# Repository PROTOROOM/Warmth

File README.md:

# Warmth
The lighting place card for YoungJi & Derrick's wedding
  - PROTOROOM 
  - by SeungBum Kim & Hoonida Kim
  - 2017.04.01

이 프로젝트의 이야기는 다음 웹페이지에서 읽어볼 수 있습니다.
Please read the whole story of Warmth on the link below. (sorry for Korean only now)

https://protoroom.github.io/Warmth/memo/story_of_warmth.html

# License
 - firmware : Artistic License 2.0
 - hardware : Creative Commons Attribution ShareAlike 3.0

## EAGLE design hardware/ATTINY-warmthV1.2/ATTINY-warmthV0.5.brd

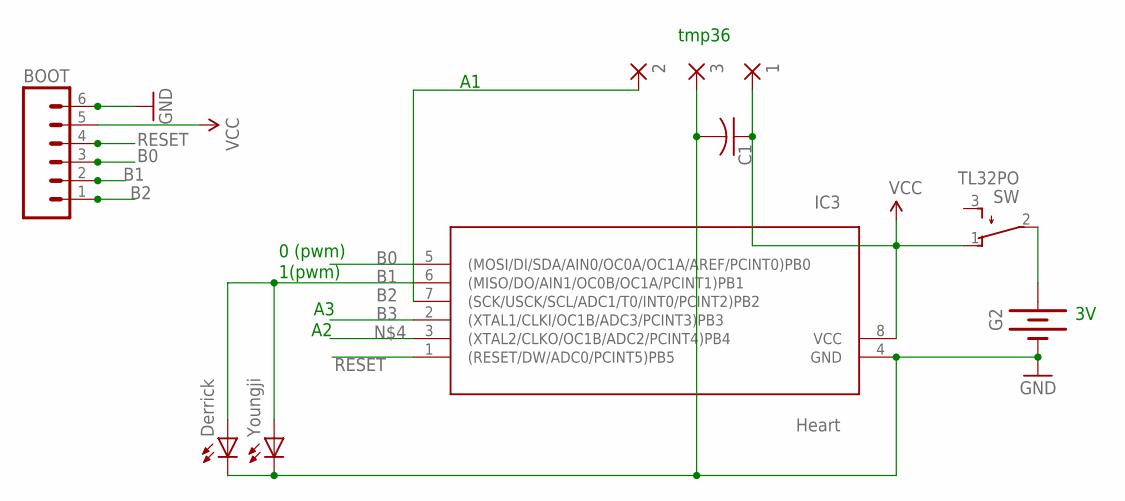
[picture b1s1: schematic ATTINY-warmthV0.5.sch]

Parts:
1, 2, 3: WIREPADSMD1,27-254; SMD1,27-2,54
BOOT: M06SIP; 1X06
C1: C-USC0805K; C0805K
G2: BATTERY20SMD; BATTCON_20MM
IC3: Heart; SOIC8
SW: TL32PO; TL3XPO
TX: Derrick; LED3MM
TX1: Youngji; LED3MM

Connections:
B0: BOOT.3, IC3.5 ((MOSI/DI/SDA/AIN0/OC0A/OC1A/AREF/PCINT0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)
B1: BOOT.2, IC3.6 ((MISO/DO/AIN1/OC0B/OC1A/PCINT1)PB1), TX.A, TX1.A
B2: 2.1, BOOT.1, IC3.7 ((SCK/USCK/SCL/ADC1/T0/INT0/PCINT2)PB2)
B3: IC3.2 ((XTAL1/CLKI/OC1B/ADC3/PCINT3)PB3)
GND: 3.1, BOOT.6, C1.2, G2.2 (-), IC3.4 (GND), TX.K (C), TX1.K (C)
unnamed: G2.1 (+), SW.2
RESET: BOOT.4, IC3.1 ((RESET/DW/ADC0/PCINT5)PB5)
VCC: 1.1, BOOT.5, C1.1, IC3.8 (VCC), SW.1 (O)

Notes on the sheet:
1(pwm)
0 (pwm)
tmp36

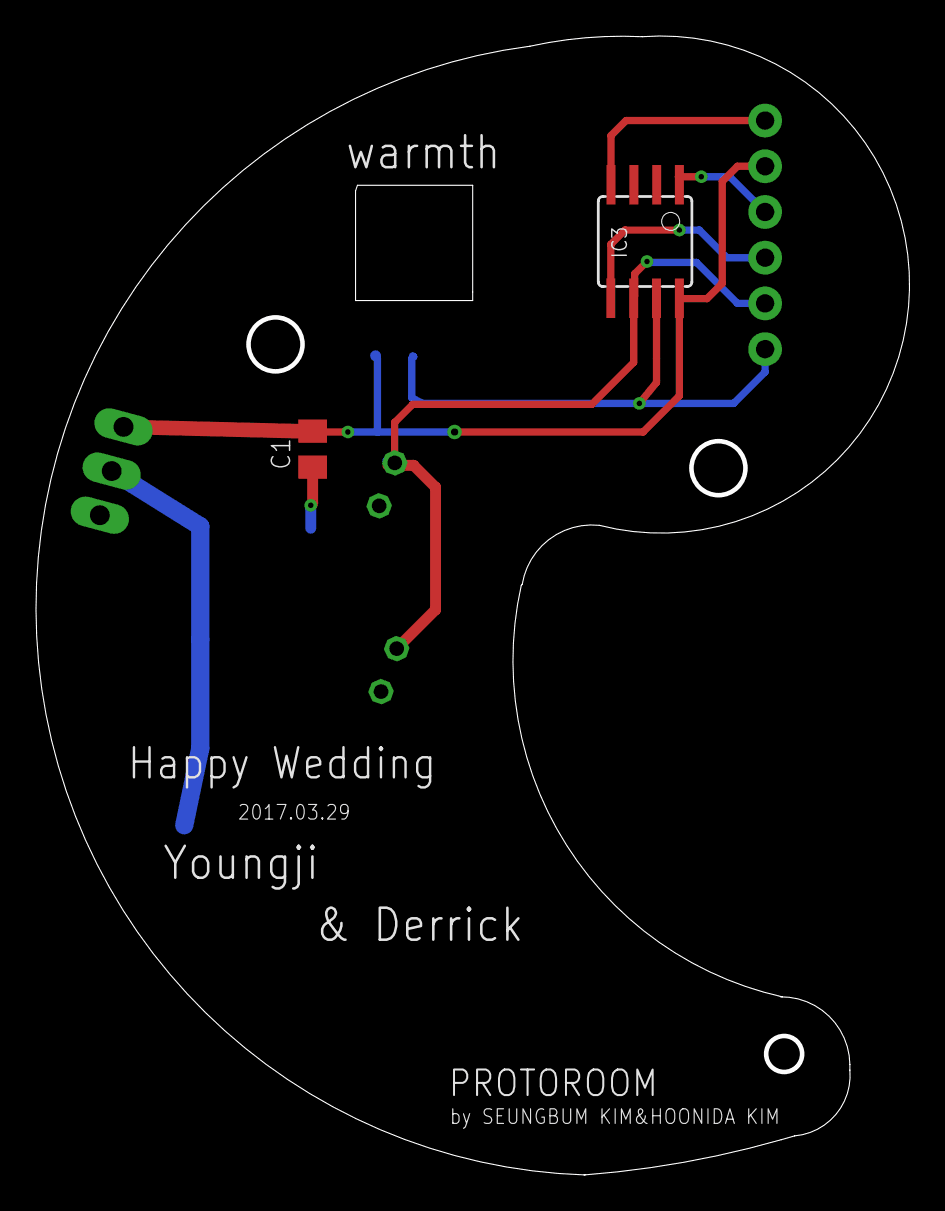
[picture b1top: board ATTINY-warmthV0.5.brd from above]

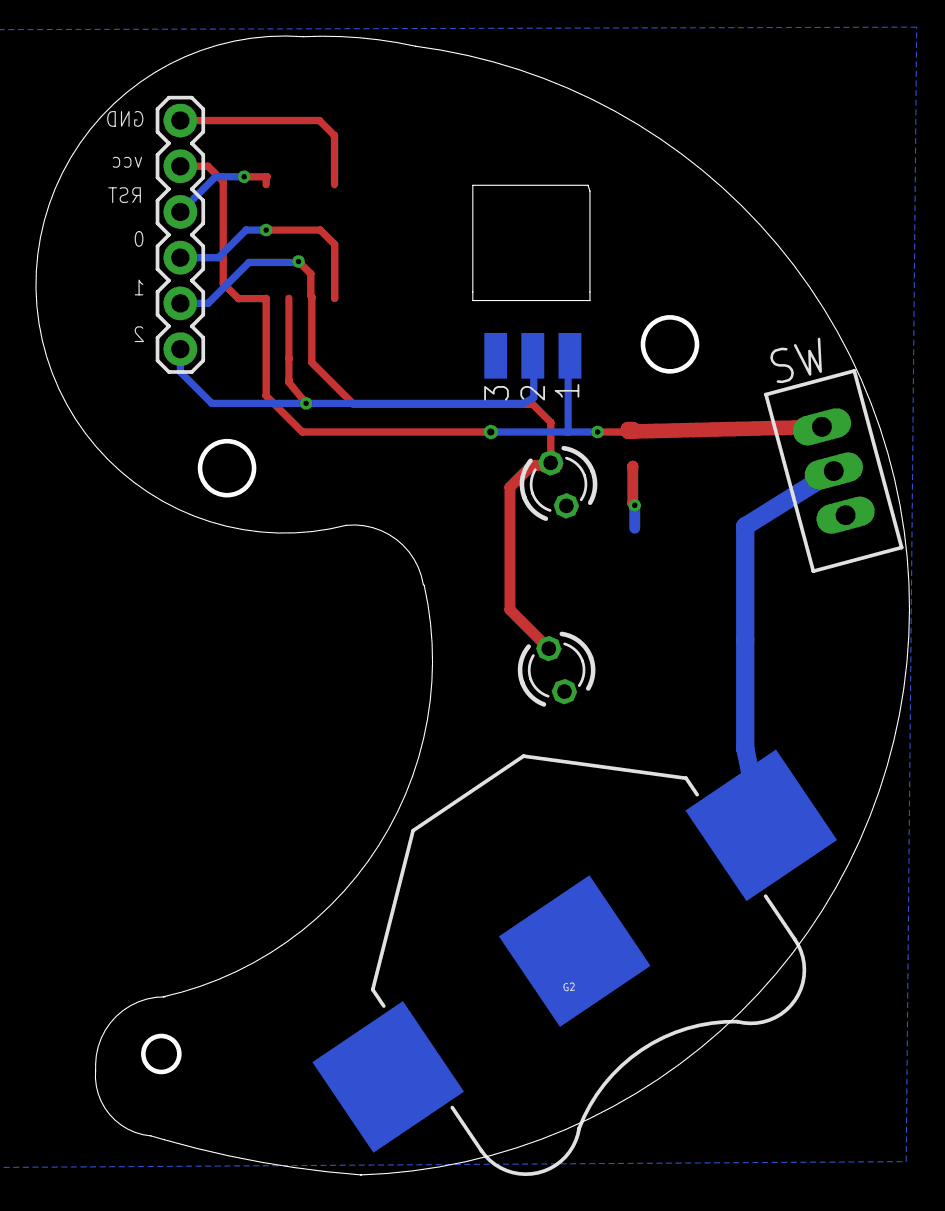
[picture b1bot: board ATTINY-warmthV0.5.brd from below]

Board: 2 copper layers, 48.5 x 63.3 mm, 10 parts (8 on the bottom side), 7 nets.

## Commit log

2017-03-19 add firmware
2017-03-19 add hardware
2017-03-25 update firmware
2017-03-29 start memo for Warmth
2017-03-29 writing memo
2017-03-29 writing memo for parts
2017-03-31 make html
2017-05-09 update images
2017-05-09 change indentation
2017-05-09 fix font size
2017-05-09 fix footnote
2017-05-11 add images
2017-05-11 update front image
2017-05-11 update story
2017-05-11 add license
2017-05-11 add part images
2017-05-11 add story
2017-05-11 add circuit image
2017-05-11 add story about clip

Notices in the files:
parts and their libraries:
SparkFun: Licensing: CC v3.0 Share-Alike You are welcome to use this library for commercial purposes.
